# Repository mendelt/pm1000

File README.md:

# Documentation for racking up Yamaha PM1000 channel strips

Requirements;
- Two channel strips in one 2U 19inch rack enclosure
- Internal power supply that provides 44V to two strips
  - We're assuming 100mA nominal power draw per channel strip 200mA peak (for now)
  - 44V (or 48V if possible) switchable phantom power
  - Uses 1x 44V or 2x 22V transformer (VA rating tbd)
- Phantom power is supplied via two 6k8 resistors and not via the center tap of the input transformer
- We're using the original Tamura input and output transformers where possible.
- Power switch on the front panel
- Power led on the front panel
- Phantom power switchable per channel
- Phantom power led per channel
- TS unbalanced instrument input

This project will include
- Instructions on how to prepare the channel strips
- PSU PCB design
- Front panel designs

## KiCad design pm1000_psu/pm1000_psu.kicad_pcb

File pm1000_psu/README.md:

# PM1000 PSU

KiCad project for the PM1000 power supply.

## Purpose

This power supply is intended to provide the DC rails for two PM1000 preamp modules and an additional phantom-power board. It accepts a transformer secondary voltage of 36 Vrms total, whether implemented as 2 × 18 V or 1 × 36 V, rectifies that AC to raw DC, and then creates the regulated rails needed by the modules. The circuit produces two separate regulated rails from the same rectified supply: the main 44 V rail that powers the PM1000 boards, and the phantom rail that feeds the microphone accessory board.

Each PM1000 board nominally draws about 20 mA, with a theoretical maximum of about twice that value, so the 44 power rail must be able to supply around 80mA.

The phantom-power section is intended to feed a standard 48 V microphone arrangement for both channels, so it must be capable of providing enough current for two connected microphones. The phantom board will need a maximum current of roughly 15 mA, plus a little margin for the board itself.

The total current drawn from the input will be around 50 mA nominally. With a maximum of 100 mA, or around twice that.

## Schematic operation

This schematic is a small linear power supply intended to generate a regulated DC output and a phantom-feed output from an AC input. It is not a transformer-isolated switch-mode converter; it is a rectifier followed by LM317 linear regulators, with the output voltages determined by the resistor ratios in the regulator networks. The design is organized into three main sections: AC rectification, regulation, and status/indicator wiring.

### 1) AC to DC conversion

The input connector J2 is fed by a 36 Vrms transformer secondary, whether that is implemented as 2 × 18 V or 1 × 36 V AC. The peak voltage is therefore 36 × √2 ≈ 50.9 V. The bridge rectifier formed by D1 through D6 drops roughly two silicon junctions, or about 2 × 0.7 V = 1.4 V, so the capacitor charges to roughly 49.5 V at light load. The schematic uses a single 2200 µF reservoir capacitor on the raw DC bus. The remaining ripple is approximately I / (2 f C), so at 100 mA with a 100 Hz full-wave ripple the ripple is about 0.23 Vpp: 0.1 / (2 × 100 × 2.2e-3) ≈ 0.23 V. C3 and C4 are additional 100 nF decoupling capacitors placed close to the regulator inputs to help suppress switching noise and short transients.

The resulting raw rail is labeled as unregulated DC in the schematic and is the source for the regulated outputs, sitting at roughly 49 V DC with a maximum of 230 mV of ripple before the LM317 regulators.

### 2) 44 V regulated outputs

There are two independent 44 V regulator channels in this schematic. U1 and U2 are separate LM317 adjustable regulators, each configured around its own resistor network and local filtering components to generate a regulated 44 V output. The resistor networks around the output/adjust nodes are the key setting: in the 44 V channels the LM317 uses an 8.2 kΩ resistor from output to adjust and a 240 Ω resistor from adjust to ground. The formula is Vout = 1.25 × (1 + Rtop / Rbottom), so for 8.2 kΩ and 240 Ω we get Vout = 1.25 × (1 + 8200 / 240) ≈ 44.0 V. This is the actual voltage set by the schematic, and it is the same ratio used for each of the two 44 V rails.

The phantom regulator U3 is a separate LM317 channel using the same 8.2 kΩ / 240 Ω feedback ratio, so it also regulates to approximately 44.0 V from the same raw DC supply. The two 44 V rails are brought out separately to J3 and J4, which are the two 44 V output connectors on the board, while the phantom rail remains isolated on its own LM317-derived output. At the maximum main load, each 44 V regulator must drop roughly 49.5 V raw DC down to 44 V and supply about 40 mA, so the dissipation in each channel is approximately (49.5 - 44) × 0.04 ≈ 0.22 W. That is still moderate for a TO-220 package.

### 3) Phantom power rail

U2 is a second LM317 regulator used for the phantom-feed section. The resistor values around R1, R2, and R3 set the output to the phantom voltage, and the network around C7, C8, C9, and C10 filters the rail and provides the local reservoir needed for a clean phantom output. The output is brought to J4, which is labeled `Phantom` and is connected to the `+Phantom` net.

This rail is used as a higher-voltage auxiliary supply intended for phantom-feed service. In the actual schematic, the phantom regulator has the same 8.2 kΩ / 240 Ω LM317 feedback ratio as the two 44 V rails, so its actual output is also approximately 44.0 V. That leaves about 5.5 V of headroom above the regulated output while the raw rectified bus sits at roughly 49.5 V, which is enough for a linear LM317 to remain in regulation under normal loading. With a 44 V phantom rail and a 15 mA maximum load, the phantom LM317 dissipates roughly (49.5 - 44) × 0.015 ≈ 0.083 W. The three regulators therefore dissipate roughly 0.22 W each at the 40 mA 44 V channel load and about 0.083 W in the phantom channel at the maximum phantom current.

### 4) LED indicators

D3 and D4 are the visible indicator LEDs in the schematic. They are fed through the resistor network R1 to R4, which are the current-limiting resistors for the LED branches rather than the LM317 feedback resistors. The exact resistor values in the schematic are 22 kΩ, and that network is used to set the indicator current in a way that is consistent with the low-current LED drive requirements. At a 44 V input rail and assuming a red LED forward drop of about 2 V, each LED branch current is approximately I = (44 - 2) / 22 000 ≈ 1.9 mA. With both indicator LEDs lit at the same time, the total LED load is roughly 2 × 1.9 mA ≈ 3.8 mA. In practice, the LED branches are intended only to provide visual status indication and do not carry the main regulator load current.

### 5) Protection

D7, D8, and D10 are diode elements placed around the rails to steer or clamp current and protect the regulators from reverse or transient conditions. They ensure that the regulated outputs are not exposed to damaging reverse-current or transient conditions while the raw rectified bus is present.

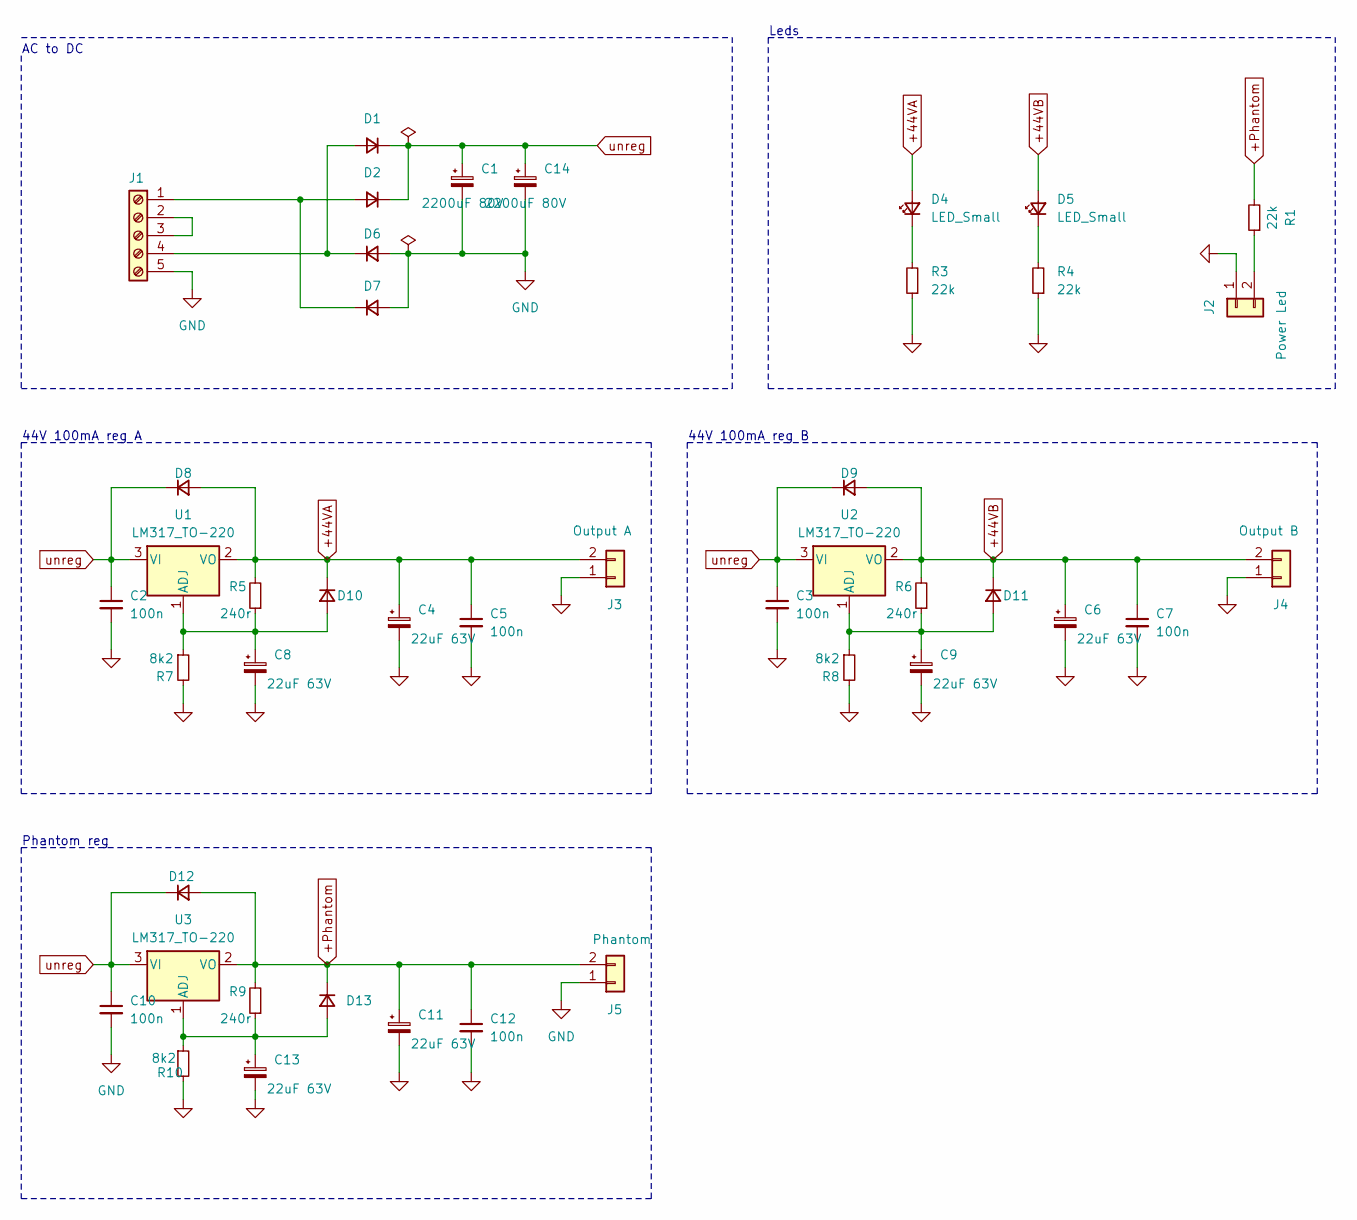
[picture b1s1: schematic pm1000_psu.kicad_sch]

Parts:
C1, C14: 2200uF 80V; CP_Radial_D22.0mm_P10.00mm_SnapIn; Mouser # 667-ECA-2AHG221B
C2, C3, C5, C7, C10, C12: 100n; C_Disc_D5.0mm_W2.5mm_P2.50mm; Mouser # 594-K104K15X7RF5TH5
C4, C6, C8, C9, C11, C13: 22uF 63V; CP_Radial_D8.0mm_P3.50mm; Mouser # 667-ECA-2AHG221B
D1, D2, D6, D7, D8, D9, D10, D11, D12, D13: D_Small; D_DO-41_SOD81_P10.16mm_Horizontal
D4, D5: LED_Small; LED_D3.0mm; Mouser # 696-SSL-LX3044HDTR
J1: Screw_Terminal_01x05; TerminalBlock_Phoenix_PT-1,5-5-5.0-H_1x05_P5.00mm_Horizontal
J2: Power Led; Molex_KK-254_AE-6410-02A_1x02_P2.54mm_Vertical
J3: Output A; Molex_KK-396_5273-02A_1x02_P3.96mm_Vertical
J4: Output B; Molex_KK-396_5273-02A_1x02_P3.96mm_Vertical
J5: Phantom; Molex_KK-254_AE-6410-02A_1x02_P2.54mm_Vertical
R1, R3, R4: 22k; R_Axial_DIN0207_L6.3mm_D2.5mm_P10.16mm_Horizontal; Mouser # 603-MFR-25FRF52-2K2
R5, R6, R9: 240r; R_Axial_DIN0207_L6.3mm_D2.5mm_P10.16mm_Horizontal; Mouser # 603-MFR-25FRF52-240R
R7, R8, R10: 8k2; R_Axial_DIN0207_L6.3mm_D2.5mm_P10.16mm_Horizontal; Mouser # 603-MFR-25FRF52-7K5
U1, U2, U3: LM317_TO-220; TO-220-3_Vertical; Mouser # 511-LM317BT

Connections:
+44VA: C4.1, C5.1, D4.2 (A), D8.2 (A), D10.1 (K), J3.2, R5.2, U1.2 (VO)
+44VB: C6.1, C7.1, D5.2 (A), D9.2 (A), D11.1 (K), J4.2, R6.2, U2.2 (VO)
+Phantom: C11.1, C12.1, D12.2 (A), D13.1 (K), J5.2, R1.2, R9.2, U3.2 (VO)
GND: C1.2, C2.2, C3.2, C4.2, C5.2, C6.2, C7.2, C8.2, C9.2, C10.2, C11.2, C12.2, C13.2, C14.2, D6.2 (A), D7.2 (A), J1.5, J2.1, J3.1, J4.1, J5.1, R3.1, R4.1, R7.2, R8.2, R10.2
unnamed: D1.2 (A), D6.1 (K), J1.4
unnamed: D2.2 (A), D7.1 (K), J1.1
unnamed: D4.1 (K), R3.2
unnamed: D5.1 (K), R4.2
unnamed: C8.1, D10.2 (A), R5.1, R7.1, U1.1 (ADJ)
unnamed: C9.1, D11.2 (A), R6.1, R8.1, U2.1 (ADJ)
unnamed: C13.1, D13.2 (A), R9.1, R10.1, U3.1 (ADJ)
unnamed: J1.2, J1.3
unnamed: J2.2, R1.1
unreg: C1.1, C2.1, C3.1, C10.1, C14.1, D1.1 (K), D2.1 (K), D8.1 (K), D9.1 (K), D12.1 (K), U1.3 (VI), U2.3 (VI), U3.3 (VI)

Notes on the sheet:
44V 100mA reg A
44V 100mA reg B
Leds
Phantom reg
AC to DC

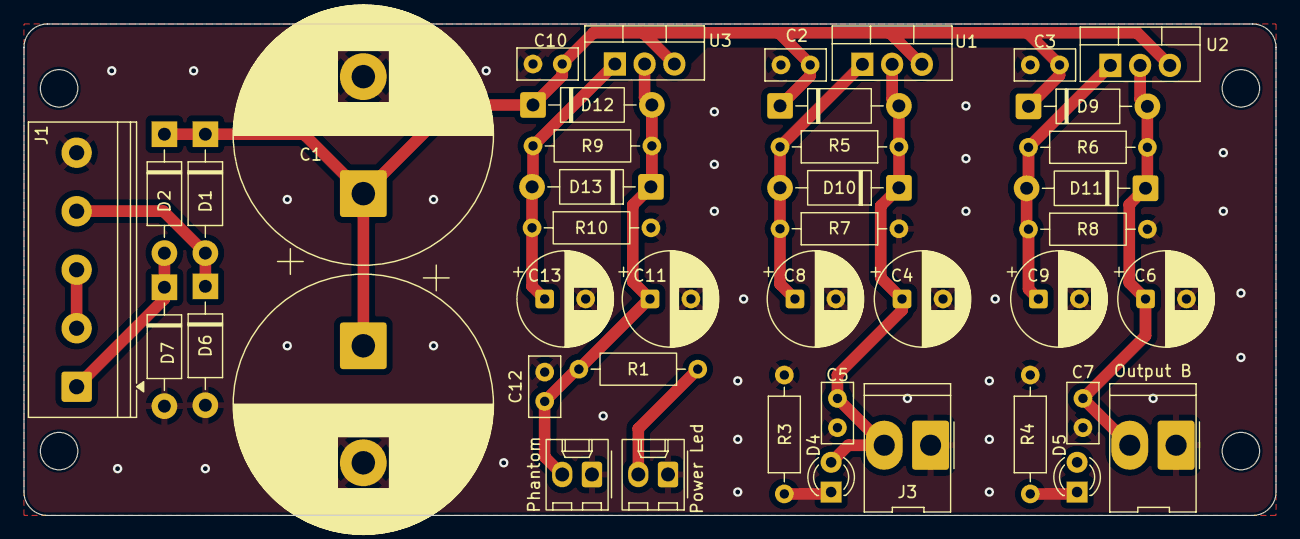
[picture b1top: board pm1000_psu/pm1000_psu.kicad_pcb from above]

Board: 2 copper layers, 107.0 x 42.0 mm, 43 parts (0 on the bottom side), 14 nets.

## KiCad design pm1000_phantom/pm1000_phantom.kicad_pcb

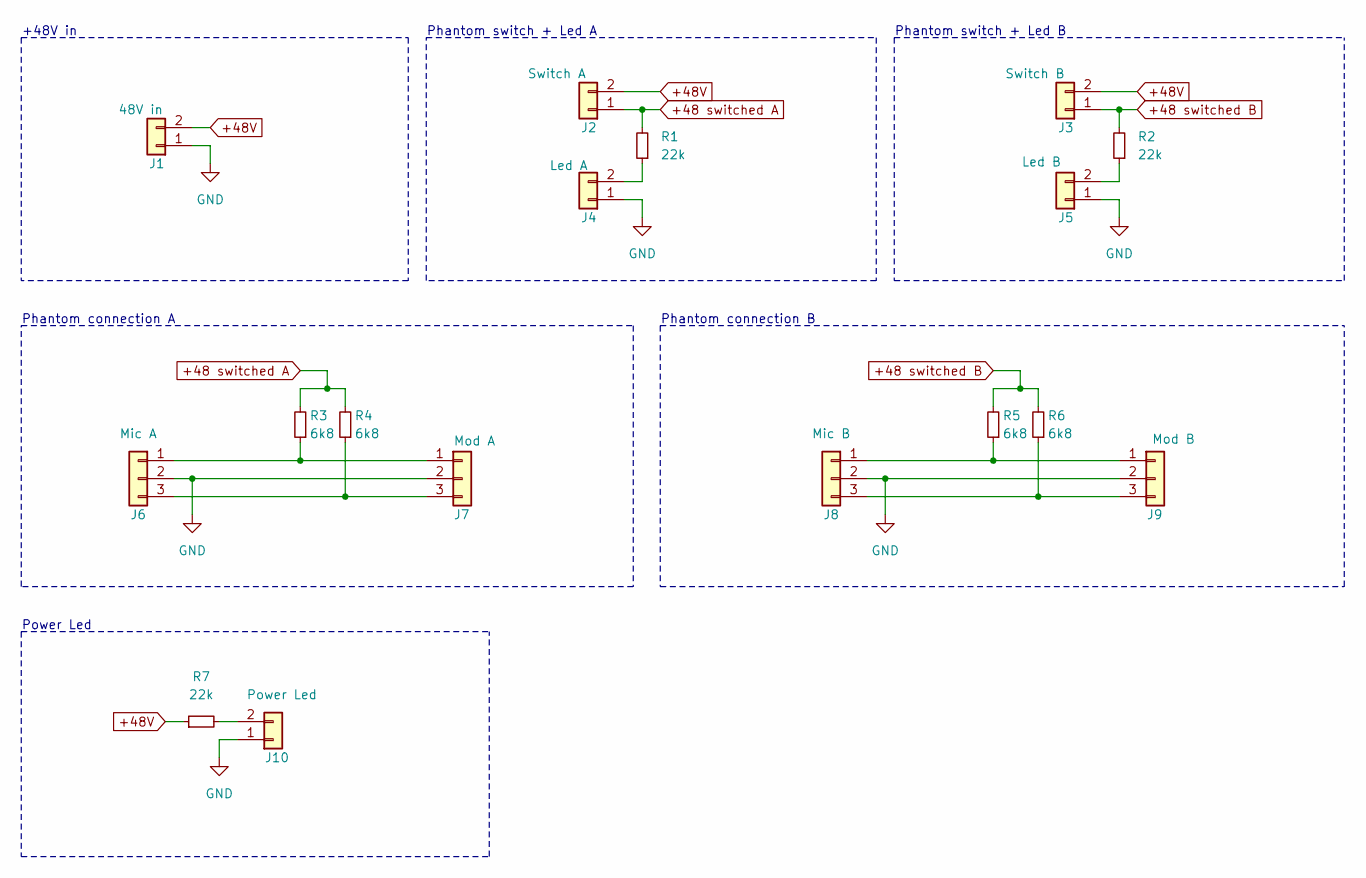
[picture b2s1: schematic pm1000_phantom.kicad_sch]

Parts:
J1: 48V in; Molex_KK-254_AE-6410-02A_1x02_P2.54mm_Vertical; Mouser # 538-22-23-2028
J2: Switch A; Molex_KK-254_AE-6410-02A_1x02_P2.54mm_Vertical; Mouser # 538-22-23-2028
J3: Switch B; Molex_KK-254_AE-6410-02A_1x02_P2.54mm_Vertical; Mouser # 538-22-23-2028
J4: Led A; Molex_KK-254_AE-6410-02A_1x02_P2.54mm_Vertical; Mouser # 538-22-23-2028
J5: Led B; Molex_KK-254_AE-6410-02A_1x02_P2.54mm_Vertical; Mouser # 538-22-23-2028
J6: Mic A; Molex_KK-254_AE-6410-03A_1x03_P2.54mm_Vertical; Mouser # 538-22-04-5032
J7: Mod A; Molex_KK-254_AE-6410-03A_1x03_P2.54mm_Vertical; Mouser # 538-22-04-5032
J8: Mic B; Molex_KK-254_AE-6410-03A_1x03_P2.54mm_Vertical; Mouser # 538-22-04-5032
J9: Mod B; Molex_KK-254_AE-6410-03A_1x03_P2.54mm_Vertical; Mouser # 538-22-04-5032
J10: Power Led; Molex_KK-254_AE-6410-02A_1x02_P2.54mm_Vertical; Mouser # 538-22-23-2028
R1, R2, R7: 22k; R_Axial_DIN0207_L6.3mm_D2.5mm_P10.16mm_Horizontal; Mouser # 603-MFR-25FRF52-2K2
R3, R4, R5, R6: 6k8; R_Axial_DIN0207_L6.3mm_D2.5mm_P10.16mm_Horizontal; Mouser # 603-MFR-25FRF52-6K8

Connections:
+48 switched A: J2.1, R1.2, R3.2, R4.2
+48 switched B: J3.1, R2.2, R5.2, R6.2
+48V: J1.2, J2.2, J3.2, R7.1
GND: J1.1, J4.1, J5.1, J6.2, J7.2, J8.2, J9.2, J10.1
unnamed: J4.2, R1.1
unnamed: J5.2, R2.1
unnamed: J6.1, J7.1, R3.1
unnamed: J6.3, J7.3, R4.1
unnamed: J8.1, J9.1, R5.1
unnamed: J8.3, J9.3, R6.1
unnamed: J10.2, R7.2

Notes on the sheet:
+48V in
Phantom connection A
Power Led
Phantom connection B
Phantom switch + Led B
Phantom switch + Led A

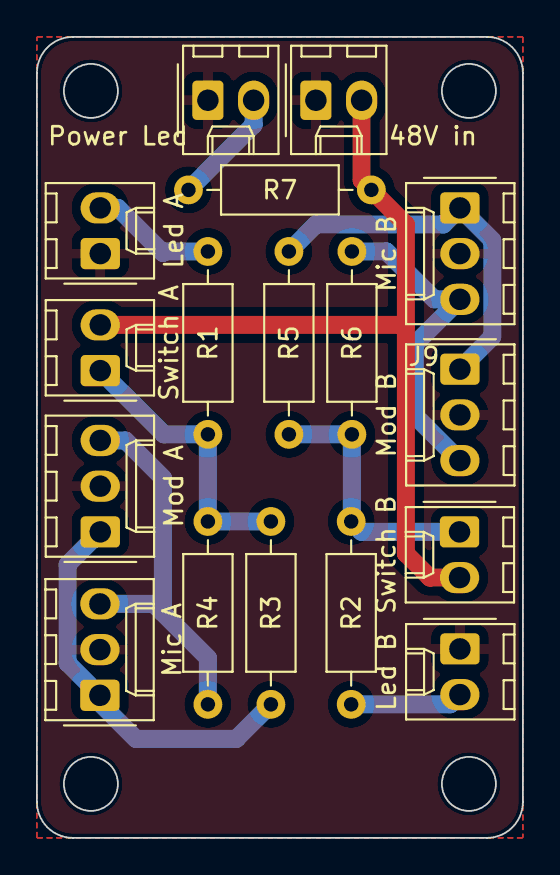
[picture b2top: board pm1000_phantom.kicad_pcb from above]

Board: 2 copper layers, 27.0 x 44.5 mm, 17 parts (0 on the bottom side), 11 nets.

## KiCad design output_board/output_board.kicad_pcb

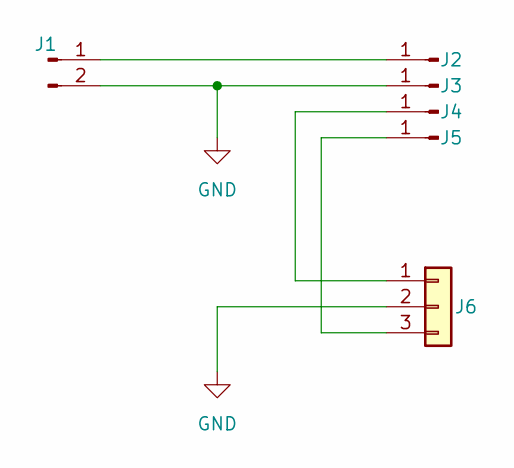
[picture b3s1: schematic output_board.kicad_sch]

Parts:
J1: Conn_01x02_Pin; SolderWire-0.5sqmm_1x02_P4.6mm_D0.9mm_OD2.1mm
J2, J3, J4, J5: Conn_01x01_Pin; SolderWirePad_1x01_SMD_1x2mm
J6: Conn_01x03; Molex_KK-254_AE-6410-03A_1x03_P2.54mm_Vertical

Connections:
GND: J1.2, J3.1, J6.2
unnamed: J1.1, J2.1
unnamed: J4.1, J6.1
unnamed: J5.1, J6.3

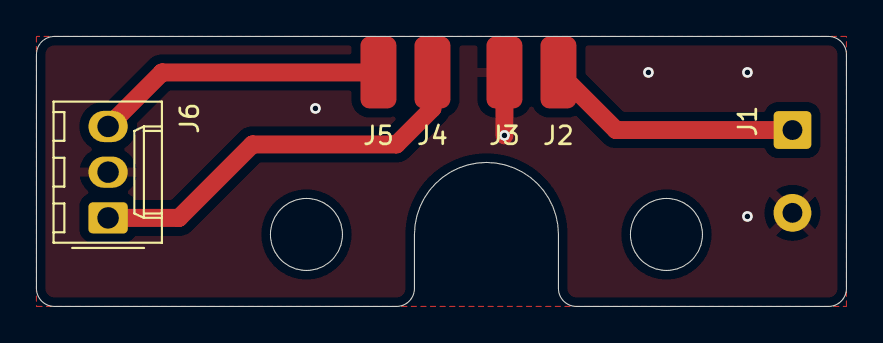
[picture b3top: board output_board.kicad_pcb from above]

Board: 2 copper layers, 45.0 x 15.0 mm, 6 parts (0 on the bottom side), 4 nets.

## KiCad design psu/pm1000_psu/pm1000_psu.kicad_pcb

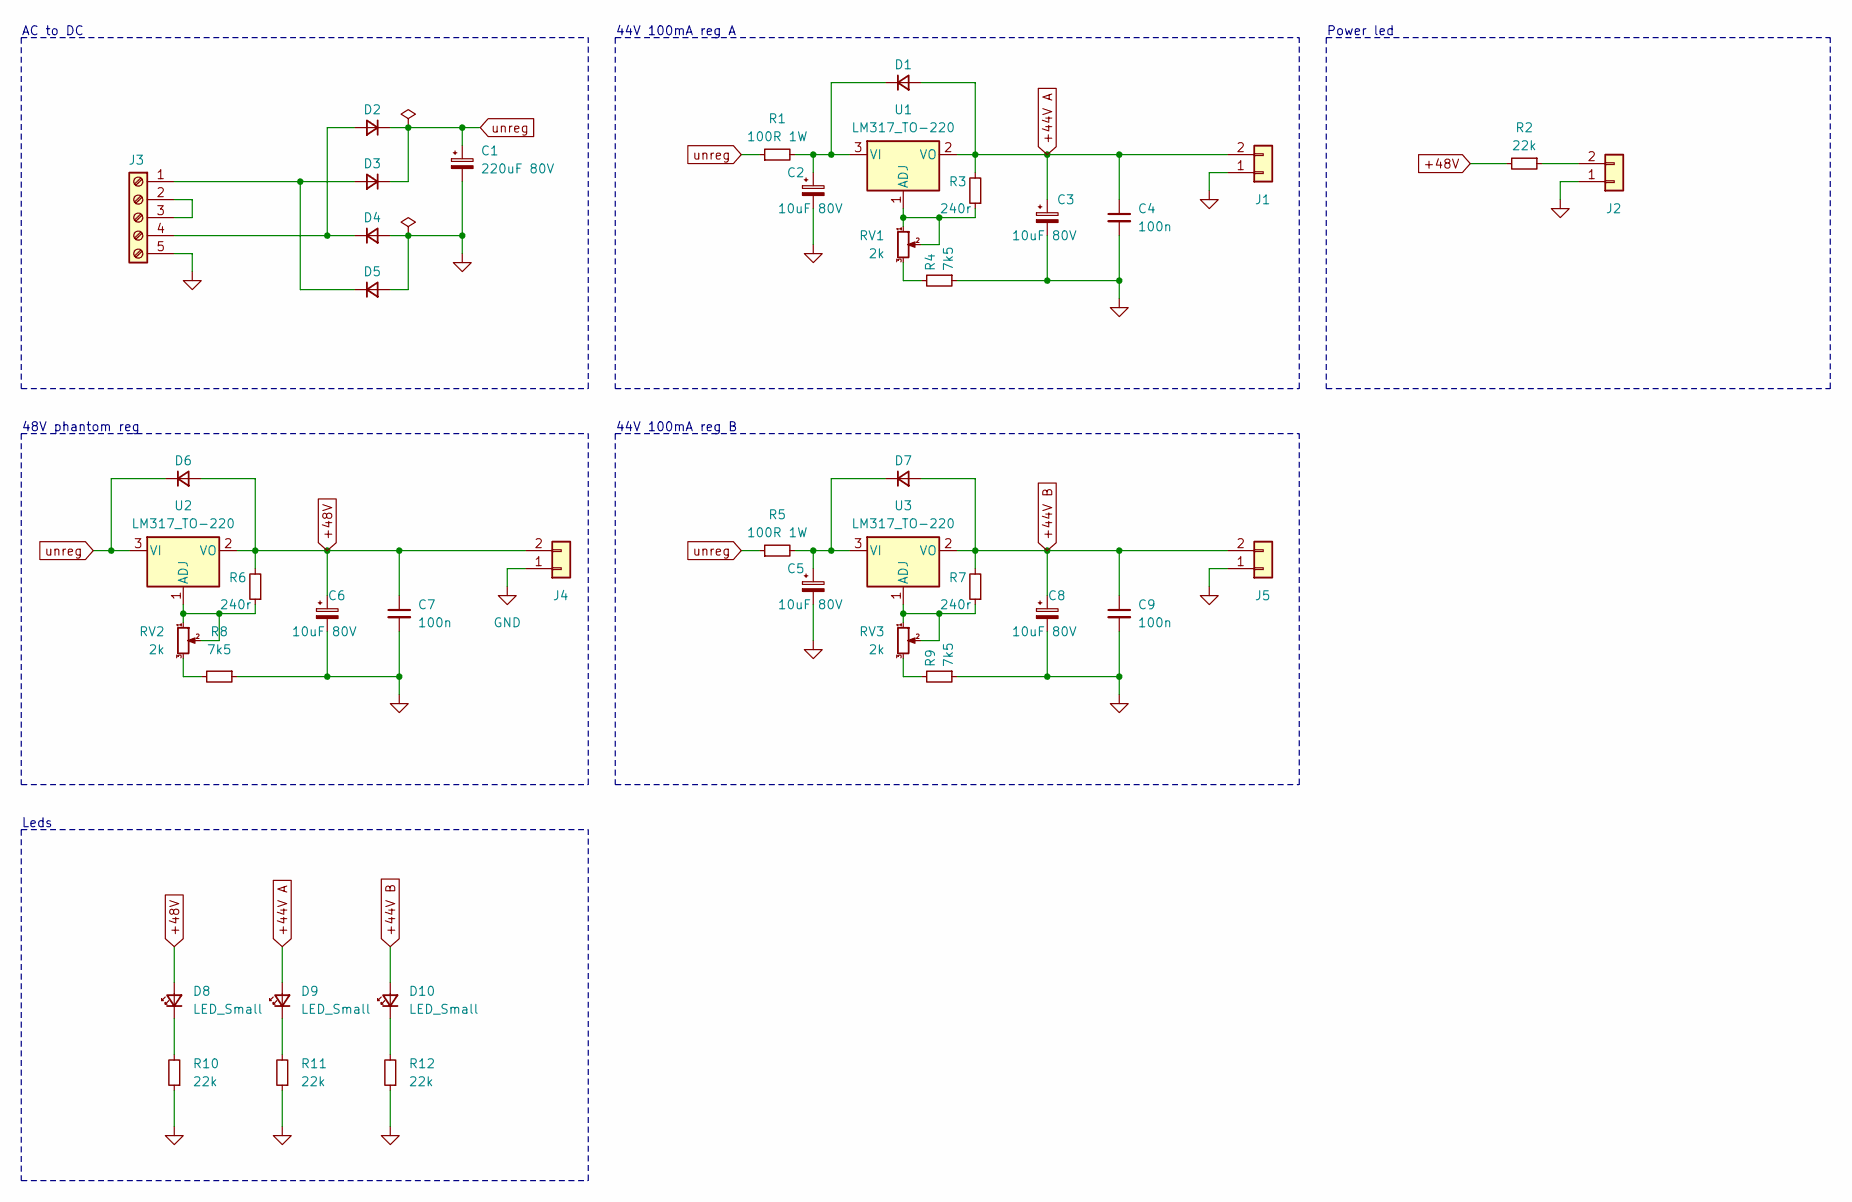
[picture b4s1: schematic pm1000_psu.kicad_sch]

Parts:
C1: 220uF 80V; CP_Radial_D12.5mm_P5.00mm; Mouser # 667-ECA-2AHG221B
C2, C3, C5, C6, C8: 10uF 80V; CP_Radial_D6.3mm_P2.50mm; Mouser # 667-ECA-2AM100I
C4, C7, C9: 100n; C_Disc_D5.0mm_W2.5mm_P2.50mm; Mouser # 594-K104K15X7RF5TH5
D1, D2, D3, D4, D5, D6, D7: 1n4004; D_DO-41_SOD81_P10.16mm_Horizontal; Mouser # 621-1N4007
D8, D9, D10: LED_Small; LED_D3.0mm; Mouser # 696-SSL-LX3044HDTR
J1, J5: Molex_KK-396_5273-02A_1x02_P3.96mm_Vertical
J2, J4: Molex_KK-254_AE-6410-02A_1x02_P2.54mm_Vertical
J3: Screw_Terminal_01x05; TerminalBlock_Phoenix_PT-1,5-5-5.0-H_1x05_P5.00mm_Horizontal
R1, R5: 100R 1W; R_Axial_DIN0411_L9.9mm_D3.6mm_P15.24mm_Horizontal; Mouser # 603-MFR100FTE52-1R
R2, R10, R11, R12: 22k; R_Axial_DIN0207_L6.3mm_D2.5mm_P10.16mm_Horizontal; Mouser # 603-MFR-25FRF52-2K2
R3, R6, R7: 240r; R_Axial_DIN0207_L6.3mm_D2.5mm_P10.16mm_Horizontal; Mouser # 603-MFR-25FRF52-240R
R4, R8, R9: 7k5; R_Axial_DIN0207_L6.3mm_D2.5mm_P10.16mm_Horizontal; Mouser # 603-MFR-25FRF52-7K5
RV1, RV2, RV3: 2k; Potentiometer_Piher_PT-10-V05_Vertical
U1, U2, U3: LM317_TO-220; TO-220-3_Vertical; Mouser # 511-LM317BT

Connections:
+44V A: C3.1, C4.1, D1.2 (A), D9.2 (A), J1.2, R3.2, U1.2 (VO)
+44V B: C8.1, C9.1, D7.2 (A), D10.2 (A), J5.2, R7.2, U3.2 (VO)
+48V: C6.1, C7.1, D6.2 (A), D8.2 (A), J4.2, R2.2, R6.2, U2.2 (VO)
GND: C1.2, C2.2, C3.2, C4.2, C5.2, C6.2, C7.2, C8.2, C9.2, D4.2 (A), D5.2 (A), J1.1, J2.1, J3.5, J4.1, J5.1, R4.1, R8.1, R9.1, R10.1, R11.1, R12.1
unnamed: C2.1, D1.1 (K), R1.2, U1.3 (VI)
unnamed: D2.2 (A), D4.1 (K), J3.4
unnamed: D3.2 (A), D5.1 (K), J3.1
unnamed: C5.1, D7.1 (K), R5.2, U3.3 (VI)
unnamed: D8.1 (K), R10.2
unnamed: D9.1 (K), R11.2
unnamed: D10.1 (K), R12.2
unnamed: J2.2, R2.1
unnamed: J3.2, J3.3
unnamed: R4.2, RV1.3
unnamed: R8.2, RV2.3
unnamed: R9.2, RV3.3
unnamed: R3.1, RV1.1, RV1.2, U1.1 (ADJ)
unnamed: R6.1, RV2.1, RV2.2, U2.1 (ADJ)
unnamed: R7.1, RV3.1, RV3.2, U3.1 (ADJ)
unreg: C1.1, D2.1 (K), D3.1 (K), D6.1 (K), R1.1, R5.1, U2.3 (VI)

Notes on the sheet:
44V 100mA reg A
Leds
44V 100mA reg B
Power led
48V phantom reg
AC to DC

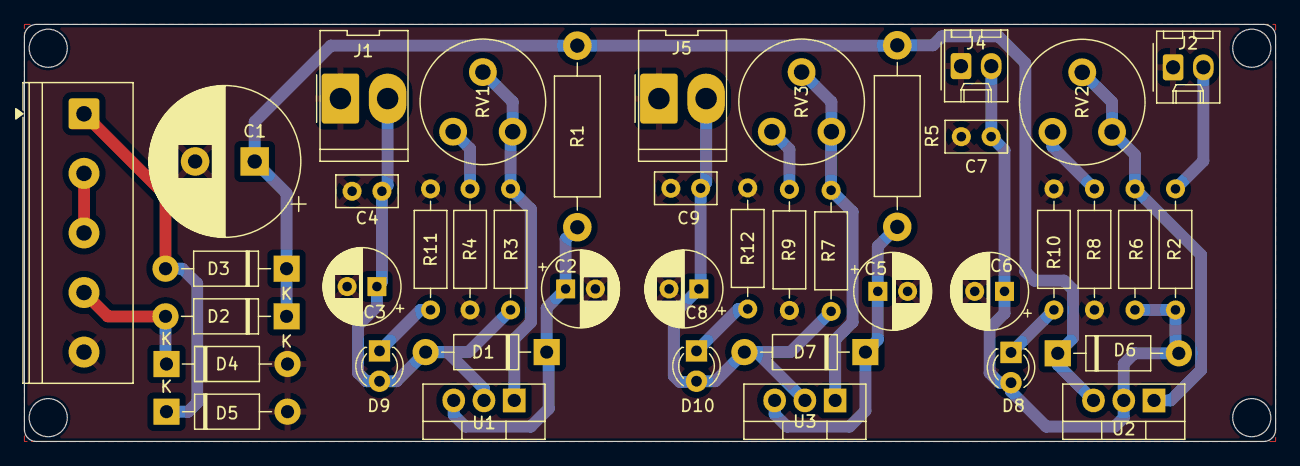
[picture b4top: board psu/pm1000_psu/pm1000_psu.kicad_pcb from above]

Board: 2 copper layers, 105.0 x 35.0 mm, 42 parts (0 on the bottom side), 20 nets.

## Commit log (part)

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2022-08-26 add psu kicad project with first schematic outline
2022-08-27 clean up schematic
2022-08-27 update schematic
    - add diode footprints
    - add reg protection diodes
    - add trimmers
    - cleanup
2022-09-11 calculate values and add some footprints
2022-09-12 add rest of the footprints
2022-09-12 split psu and phantom pcb
2022-09-14 rename phantom board files and do some placement
2022-09-18 layout and route pcb board
2022-09-20 update phantom board
2022-09-20 update .gitignore to exclude output files
2022-09-25 update boms with (some) mouser part numbers add 100n capacitors add power leds add frontpanel power led connector to psu board
2022-10-01 add power pins for cpu
2022-10-01 rework the psu layout a bit
2022-10-01 simplify filter stages for 44v channels
2022-10-17 increase pre reg filter r to 100ohm to accomodate for the lower current
2022-10-17 new layout
2022-10-19 route psu pcb
2022-10-19 phantom board: connect mic input gnd
2022-10-19 route phantom pcb
2022-11-08 refill
2022-12-30 update component values and mouser numbers for easy ordering
2026-02-15 clean up projects and update to kicad 9
2026-02-15 psu schematic, add 5-terminal input with ground connection
2026-02-15 psu: set clearances
2026-02-15 phantom: increase board size, better clearances
2026-02-15 set led resistors to 22k, place new psu terminal block
2026-02-15 remove backup zips
2026-02-15 clean up output board
2026-02-15 clean up project structure, organize psu silkscreen
